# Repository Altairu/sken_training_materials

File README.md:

# sken_training_materials
sken_講習資料

https://Altairu.github.io/sken_training_materials/

使い方に関しては，サイト内の「wiki使い方」をご覧ください・

```bash
mkdocs gh-deploy

& "$env:USERPROFILE\AppData\Roaming\Python\Python311\Scripts\mkdocs.exe" gh-deploy

```

## 必要な環境構築

1. **Python のインストール**  
   Python 3.8 以上が必要です。以下のコマンドでインストールを確認してください。
   ```bash
   python3 --version
   ```

2. **`pip` のインストール**  
   Python パッケージマネージャー `pip` をインストールします。
   ```bash
   sudo apt update
   sudo apt install python3-pip
   ```

3. **`mkdocs` とテーマのインストール**  
   MkDocs と Material for MkDocs をインストールします。
   ```bash
   pip install mkdocs
   pip install mkdocs-material
   ```

4. **必要なパッケージのバージョン確認**  
   以下のバージョンがインストールされていることを確認してください。
   ```
   python                       3.9.5
   mkdocs                       1.4.2
   mkdocs-material              8.5.11
   mkdocs-material-extentions   1.1.1
   pymdown-extensions           9.9
   ```

5. **ローカルサーバーの起動**  
   以下のコマンドでローカルサーバーを起動し、サイトを確認できます。
   ```bash
   mkdocs serve
   ```

## 資料追加の手順

1. **資料ファイルを作成する**  
   `docs/training_materials` フォルダ内の適切なカテゴリに新しい資料ファイル（例: `new_material.md`）を作成します。

2. **`mkdocs.yml` にナビゲーションを追加する**  
   `mkdocs.yml` ファイルを編集し、新しい資料へのリンクをナビゲーションに追加します。例:
   ```yaml
   nav:
     - 新しい資料: training_materials/新しい資料/new_material.md
   ```

3. **ローカルで確認する**  
   以下のコマンドを実行してローカルサーバーを起動し、変更を確認します。
   ```bash
   mkdocs serve
   ```

4. **変更をコミットしてプッシュする**  
   変更を Git にコミットして GitHub にプッシュすると、GitHub Actions により自動的にデプロイ（`mkdocs gh-deploy`）が行われます。
   ```bash
   git add .
   git commit -m "新しい資料を追加"
   git push origin main
   ```

5. **公開されたサイトを確認する**  
   `https://Altairu.github.io/sken_training_materials/` にアクセスして、資料が正しく追加されていることを確認します。

## 自動通知機能の概要

このプロジェクトには、以下の機能を持つ自動通知システムが追加されました：

1. **変更検知**:
   - Gitリポジトリの差分を検出し、変更されたファイルを特定します。

2. **重要性判定**:
   - Google Generative AI APIを使用して、変更内容を要約し、重要性を判定します。

3. **Discord通知**:
   - 重要な変更があった場合、要約を含むメッセージをDiscordに送信します。

### 必要な設定

- **Google Generative AI APIキー**:
  - 環境変数 `GOOGLE_API_KEY` に設定してください。

- **Discord Webhook URL**:
  - 環境変数 `DISCORD_WEBHOOK_URL` に設定してください。

### 実行方法

以下のコマンドでスクリプトを実行できます：
```bash
python notify_changes.py
```

### スクリプトの場所

スクリプトはプロジェクトのルートディレクトリに配置されています。

## コントリビューションの手順

他の人がこのリポジトリに変更を加えるには、以下の手順を実行してください。

1. **リポジトリをフォークする**  
   GitHub 上でこのリポジトリをフォークします。

2. **ローカルにクローンする**  
   フォークしたリポジトリをローカル環境にクローンします。
   ```bash
   git clone https://github.com/<あなたのGitHubユーザー名>/sken_training_materials.git
   cd sken_training_materials
   ```

3. **変更を加える**  
   必要な資料を追加・編集し、`mkdocs.yml` にナビゲーションを追加します。

4. **変更をコミットする**  
   変更をステージングしてコミットします。
   ```bash
   git add .
   git commit -m "資料を追加/編集"
   ```

5. **プルリクエストを作成する**  
   GitHub 上でフォークしたリポジトリからオリジナルのリポジトリに対してプルリクエストを作成します。

6. **レビューを待つ**  
   プルリクエストが承認されるまで待ちます。必要に応じて修正を行ってください。

### 直接編集を希望する場合

直接リポジトリを編集したい場合は、[こちら](https://x.com/Flying___eagle) まで連絡してください。  
確認後、Collaborators に追加します。

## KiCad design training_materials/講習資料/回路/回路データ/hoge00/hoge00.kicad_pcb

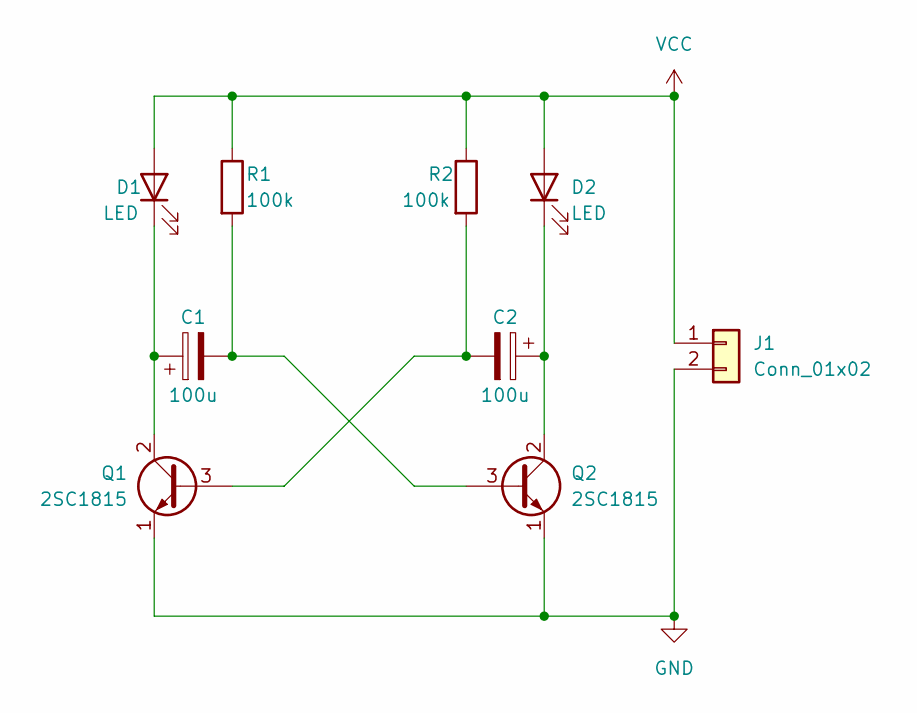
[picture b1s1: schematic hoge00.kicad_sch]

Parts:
C1, C2: 100u; CP_Radial_D5.0mm_P2.00mm
D1, D2: LED; LED_D3.0mm
J1: Conn_01x02; PinHeader_1x02_P2.54mm_Vertical
Q1, Q2: 2SC1815; TO-92_Inline_Wide
R1, R2: 100k; R_Axial_DIN0207_L6.3mm_D2.5mm_P10.16mm_Horizontal

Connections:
GND: J1.2, Q1.1 (E), Q2.1 (E)
unnamed: C1.1, D1.1 (K), Q1.2 (C)
unnamed: C2.1, D2.1 (K), Q2.2 (C)
unnamed: C2.2, Q1.3 (B), R2.2
unnamed: C1.2, Q2.3 (B), R1.2
VCC: D1.2 (A), D2.2 (A), J1.1, R1.1, R2.1

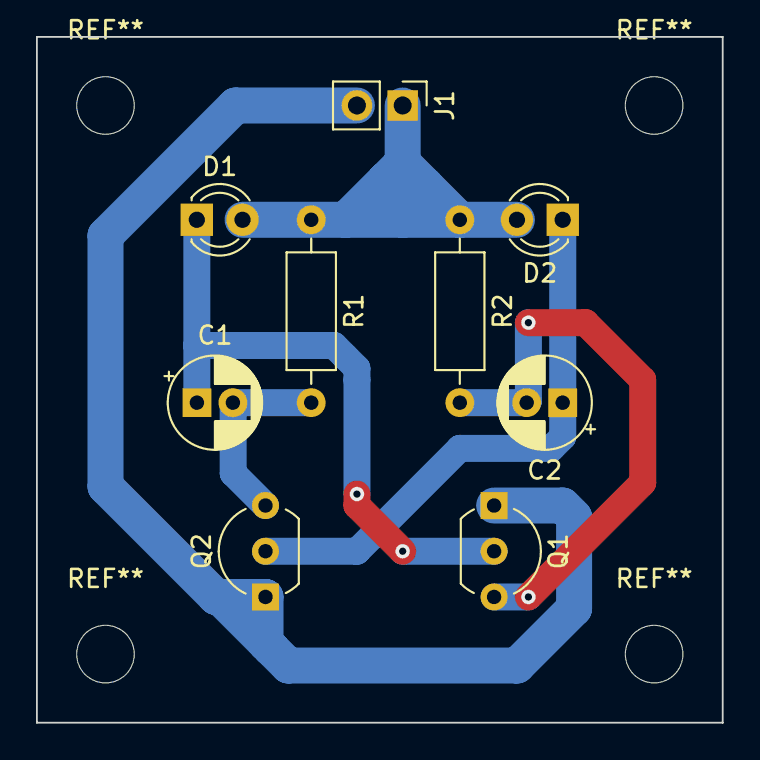
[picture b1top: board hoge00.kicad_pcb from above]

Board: 2 copper layers, 38.1 x 38.1 mm, 9 parts (0 on the bottom side), 6 nets.

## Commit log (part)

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2025-04-05 Deployed 8177294 with MkDocs version: 1.6.1
2025-04-05 new1
2025-04-05 new3
2025-04-05 Deployed 88057c9 with MkDocs version: 1.6.1
2025-04-05 Deployed 7b7d013 with MkDocs version: 1.6.1
2025-04-05 Deployed 1487b17 with MkDocs version: 1.6.1
2025-04-05 Deployed 2e3ce8f with MkDocs version: 1.6.1
2025-04-05 Deployed 4227882 with MkDocs version: 1.6.1
2025-04-05 neww
2025-04-06 hoge
2025-04-06 Deployed a72a1fb with MkDocs version: 1.6.1
2025-04-06 Deployed b8bc94b with MkDocs version: 1.6.1
2025-04-13 Deployed 2394981 with MkDocs version: 1.6.1
2025-04-13 Deployed 7a23cf7 with MkDocs version: 1.6.1
2025-04-24 Deployed 499f3d6 with MkDocs version: 1.6.1
2025-04-24 Deployed 93b165c with MkDocs version: 1.6.1
2025-04-24 Deployed 1d596b4 with MkDocs version: 1.6.1
2025-04-24 Deployed 3244e60 with MkDocs version: 1.6.1
2025-04-24 Deployed af00fed with MkDocs version: 1.6.1
2025-04-24 Deployed af9ba8f with MkDocs version: 1.6.1
2025-04-25 shin
2025-04-25 Deployed d49040a with MkDocs version: 1.6.1
2025-04-25 Deployed d93237b with MkDocs version: 1.6.1
2025-04-25 Deployed ecfb64d with MkDocs version: 1.6.1
2025-04-25 neew
2025-04-25 Deployed 407e582 with MkDocs version: 1.6.1
2025-04-25 Deployed 67956ed with MkDocs version: 1.6.1
2025-04-25 Deployed d6a64ac with MkDocs version: 1.6.1
2025-04-25 nonnew
2025-04-25 Deployed 3efc483 with MkDocs version: 1.6.1
2025-04-25 Deployed bcd3b9d with MkDocs version: 1.6.1
2025-04-25 Deployed 4cb15a2 with MkDocs version: 1.6.1
2025-04-28 Deployed ae902a5 with MkDocs version: 1.6.1
2025-04-28 Deployed b9beec2 with MkDocs version: 1.6.1
2025-04-28 Deployed 54c068f with MkDocs version: 1.6.1
2025-04-28 Deployed e4489f4 with MkDocs version: 1.6.1
2025-04-28 Deployed 1069589 with MkDocs version: 1.6.1
2025-04-28 Deployed f524f20 with MkDocs version: 1.6.1
2025-04-28 Deployed 76fef04 with MkDocs version: 1.6.1
2025-04-29 Deployed 7f4b1b8 with MkDocs version: 1.6.1
2025-04-29 Deployed 7c6317d with MkDocs version: 1.6.1
2025-04-29 Deployed a4afbba with MkDocs version: 1.6.1
2025-04-29 Deployed aa57ad1 with MkDocs version: 1.6.1
2025-04-30 Deployed f0d1f3c with MkDocs version: 1.6.1
2025-05-01 enwnw
2025-05-01 Deployed 72b9994 with MkDocs version: 1.6.1
2025-05-01 Deployed 266928c with MkDocs version: 1.6.1
2025-05-01 Deployed 1843753 with MkDocs version: 1.6.1
2025-05-01 Deployed 934821e with MkDocs version: 1.6.1
2025-05-01 Deployed b057e5a with MkDocs version: 1.6.1
2025-05-01 Deployed 3515d58 with MkDocs version: 1.6.1
2025-05-01 Deployed e6820ec with MkDocs version: 1.6.1
2025-05-02 Deployed 648e60e with MkDocs version: 1.6.1
2025-05-02 Deployed 0d7d2c3 with MkDocs version: 1.6.1
2025-05-02 python部分アップデート
2025-05-07 CI修正
2025-05-07 CI修正③
2025-05-13 Implement code changes to enhance functionality and improve performance
2025-05-13 Deployed 479f05e with MkDocs version: 1.6.1
2025-05-13 Refactor code structure for improved readability and maintainability
2025-05-13 ドライバーのインストール手順を整理し、重複を削除して明確化
2025-05-13 Deployed 7eb15b6 with MkDocs version: 1.6.1
2025-05-13 Refactor code formatting in Python training materials
    - Adjusted spacing in function definitions for consistency across multiple exercises in index.html files.
    - Updated class definitions and method signatures to improve readability in Python examples.
    - Enhanced formatting in exception handling and context manager sections for better clarity.
    - Ensured uniformity in code presentation across various HTML files in the training materials.
2025-05-13 Deployed e33a1a1 with MkDocs version: 1.6.1
2025-05-13 Add author note to CH552_2 index.html
2025-05-20 プログラミングガイドのLED接続ピンを修正し、ボタン押下時のLED制御コードを更新。新しい講習テストコードを追加。
2025-05-20 Deployed c9f9bf7 with MkDocs version: 1.6.1
2025-05-20 Refactor code formatting in Python training materials
    - Added spaces for better readability in function definitions across multiple HTML files.
    - Updated examples in the Python training materials to enhance clarity and maintain consistency in formatting.
    - Ensured that all code snippets follow a uniform style for improved learning experience.
2025-05-20 PWMの例を追加し、LEDの明るさを変化させるプログラムを実装
2025-05-20 Deployed 6ea329c with MkDocs version: 1.6.1
2025-05-20 PWMの例を更新し、LEDの明るさを変化させるプログラムを簡素化
2025-05-20 Deployed f53668d with MkDocs version: 1.6.1
2025-05-20 Refactor PWM example in CH552 training material: update setup and loop functions to use analogWrite for LED brightness control, simplifying the code and improving clarity.
2025-05-20 PWMの例を修正: PWM出力ピンを12から15に変更し、analogWriteを使用してデューティ比を制御するコードを更新
2025-05-20 Deployed c1ae22b with MkDocs version: 1.6.1
2025-05-20 Update PWM example in CH552_1 index.html to use pin 15 instead of pin 12 for analogWrite functionality
2025-06-11 SolidEdge2025の資料追加
2025-06-11 ソリッドエッジ2025資料追加
2025-06-11 Deployed de64413 with MkDocs version: 1.6.1
2025-06-11 Refactor code structure and remove redundant changes
2025-06-11 Tipセクションのフォーマットを統一し、見出しを追加して可読性を向上させました
2025-06-11 Deployed 4e16617 with MkDocs version: 1.6.1
2025-06-11 Refactor tips and notes in SE2 index.html to use admonition format for better readability and consistency
2025-06-11 Deployed affd05d with MkDocs version: 1.6.1
2025-06-11 Deployed 3cb0df3 with MkDocs version: 1.6.1
2025-06-11 Add author note to SE2 training material
    - Included a note section in the SE2 index.html file to credit the author, Mio Saito.
2025-08-21 Deployed 6d180f7 with MkDocs version: 1.6.1
2025-08-21 Deployed 49acb48 with MkDocs version: 1.6.1
2025-08-21 SolidEdgeでギヤ設計の記事を追加
2025-09-24 サーボモーター制御のサンプルコードを改善し、ソフトウェアサーボの実装を追加しました
2025-09-24 Deployed e2062d8 with MkDocs version: 1.6.1
2025-09-24 ROS2のWebSocket通信に関する説明を追加し、PC間でのトピック共有機能について言及
2025-09-24 Deployed 4009f44 with MkDocs version: 1.6.1
2025-09-24 Add explanation for WebSocket implementation in ROS communication
    - Updated the section discussing the choice of communication method to include details about the ability to share topics over the same network in ROS, indicating that WebSocket implementation may not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
2025-12-12 feat: add ref forwarding and display names to Textarea and Input components
2025-12-12 Deployed ec3480d with MkDocs version: 1.6.1
2025-12-12 feat: Generate initial static site output including HTML, CSS, JavaScript, and search assets.
2025-12-12 記事追加: AIコーディングに関する記事
2026-03-05 回路モジュール記事追加
2026-03-05 順序変更
2026-03-05 Deployed d29eb02 with MkDocs version: 1.6.1
2026-03-05 Deployed 82f97d1 with MkDocs version: 1.6.1
2026-03-23 Add environment setup guide for STM32 development using Visual Studio Code
    - Created a comprehensive markdown document detailing the installation of necessary tools including STM32CubeMX, STM32CubeCLT, and STM32 VS Code Extension.
    - Included step-by-step instructions for project creation using STM32CubeMX.
    - Provided guidance on importing projects into VS Code, building, and debugging STM32 applications.
    - Added references to external resources for further learning.
2026-03-23 Deployed b88e5d9 with MkDocs version: 1.6.1
2026-03-23 Deployed 8b5355e with MkDocs version: 1.6.1
2026-03-26 Deployed 1f297a0 with MkDocs version: 1.6.1
2026-03-26 ライブラリ使い方を追加
2026-03-26 URL変更
2026-03-26 Deployed fcd5996 with MkDocs version: 1.6.1
2026-03-26 Deployed 54e1818 with MkDocs version: 1.6.1
2026-03-26 Deployed df618cf with MkDocs version: 1.6.1
2026-03-26 Deployed 3155159 with MkDocs version: 1.6.1
2026-04-11 Deployed ee02109 with MkDocs version: 1.6.1
2026-04-11 Update motor driver documentation with PWM frequency recommendations for ALTAIR_MD_V7 and ALTAIR_MD_V8
2026-04-11 Deployed be8633f with MkDocs version: 1.6.1
2026-04-11 PID制御機能の追加とドキュメントの更新
    - PID制御機能を強化するため、新機能「Pid_setGainWithLimit」と「Pid_setInvert」を追加しました。
    - 積分制限と出力反転の設定を含むようにPid構造体を更新しました。
    - PID制御パラメータの変更点と使用例を反映させるため、ドキュメントを拡充しました。
    - 新機能に伴う動作を明確にするため、既存機能の説明を改善しました。
2026-04-11 Deployed e0677b1 with MkDocs version: 1.6.1
2026-04-11 Update kinematics initialization and example usage in STM32CubeIDE documentation
    - Added main function to demonstrate kinematics initialization.
    - Set kinematics mode, robot diameter, and wheel radius in the main function.
    - Updated example to include speed calculation for motors without PID control.
2026-04-15 Altair_moduleで使用するモジュールプログラムに関する記事を追加
2026-04-15 Deployed b5717a2 with MkDocs version: 1.6.1
2026-04-16 Deployed 7422e6c with MkDocs version: 1.6.1
2026-04-17 Deployed ed844e6 with MkDocs version: 1.6.1
2026-04-17 Deployed 0dc785d with MkDocs version: 1.6.1
2026-04-17 Update CAN communication specifications and add GUI tool documentation
    - Updated CAN communication specifications for all CAN1 to include 1Mbps in the headings and links.
    - Added new GUI tools for mdd_gui_ubuntu.py and servo_gui_ubuntu.py with installation instructions and usage guidelines.
    - Revised parameter settings and control execution modes for motors, including detailed payload structures and error codes.
    - Improved formatting for better readability and consistency throughout the documentation.
2026-04-21 Deployed 5eeef1c with MkDocs version: 1.6.1
2026-04-22 PlatformIO記事追加
2026-04-22 Deployed 990ca36 with MkDocs version: 1.6.1
2026-04-22 mbed記事追加
2026-04-23 Deployed 74e5191 with MkDocs version: 1.6.1
2026-04-23 Deployed 25da25f with MkDocs version: 1.6.1
2026-04-23 Enhance PID control explanation by converting bullet points to a list format for better readability in the training materials.
2026-04-23 Deployed 35c9ab7 with MkDocs version: 1.6.1
2026-04-23 Deployed 9cc0fd0 with MkDocs version: 1.6.1
2026-04-23 画像パスを修正し、データ作成の説明を更新
2026-04-23 Deployed 3052b6b with MkDocs version: 1.6.1
2026-04-23 Update SolidEdge training materials links and titles
    - Changed links in multiple index.html files to point to the correct SolidEdge training sections.
    - Updated display names for training sections to reflect accurate content:
    - "SolidEdge2025" changed to "SolidEdgeの基本操作"
    - "SolidEdgeでギヤ設計" remains unchanged.
    - Ensured consistency across all training material pages.
2026-04-23 Deployed 2384936 with MkDocs version: 1.6.1
2026-04-23 Fix hyperlink formatting in NCVC installation instructions
2026-04-23 Deployed bebe6e9 with MkDocs version: 1.6.1
2026-04-24 Deployed 480fa49 with MkDocs version: 1.6.1
2026-04-24 NCVC記事更新
2026-04-24 Deployed cb78fb4 with MkDocs version: 1.6.1
2026-05-01 Deployed 023aa4c with MkDocs version: 1.6.1
2026-05-01 Implement code structure updates and remove redundant sections
2026-05-01 Deployed fb270fa with MkDocs version: 1.6.1
2026-05-01 モジュールの使い方記事更新
2026-05-01 Update GitHub login instructions in training materials
    - Removed sensitive information regarding GitHub password from the registration steps for SkenGitHub.
2026-05-01 Deployed e9c6feb with MkDocs version: 1.6.1
2026-05-01 Update SkenGitHub registration section to indicate admin use
2026-05-08 docs: add index page for training materials documentation
2026-05-08 feat: add GitHub Actions workflow to automate MkDocs deployment to GitHub Pages and update documentation accordingly
2026-05-08 機械班 伝達講習
2026-05-08 軸締結 追加
2026-05-09 chore: update documentation site configuration in mkdocs.yml
2026-05-09 リンク機構
2026-05-09 docs: add initial index documentation page
2026-05-14 docs: update MDD documentation to include encoder data transmission details
2026-05-14 Deployed 7f428a6 with MkDocs version: 1.6.1
2026-05-20 docs: update navigation and configuration in mkdocs.yml
2026-05-20 Please provide the code changes or file diffs you would like me to summarize.
2026-05-20 docs: update mkdocs.yml configuration settings
2026-05-20 chore: update navigation and configuration settings in mkdocs.yml
2026-05-20 docs: update navigation and configuration settings in mkdocs.yml
2026-05-20 docs: initialize index documentation file
2026-05-20 docs: initialize documentation index page
2026-05-20 docs: add index page to training materials documentation
2026-06-08 polyfill.io サプライチェーン攻撃対策
